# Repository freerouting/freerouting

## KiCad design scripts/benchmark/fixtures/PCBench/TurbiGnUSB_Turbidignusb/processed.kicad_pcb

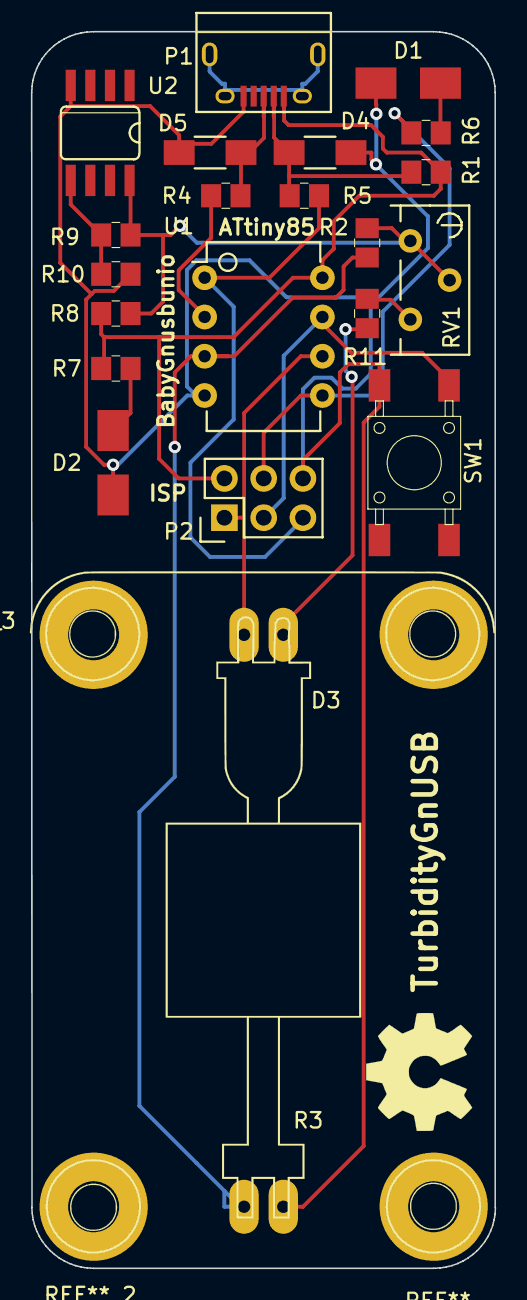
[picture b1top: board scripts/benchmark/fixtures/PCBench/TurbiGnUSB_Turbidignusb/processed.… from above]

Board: 2 copper layers, 30.0 x 80.0 mm, 22 parts (0 on the bottom side), 16 nets.

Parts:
D1, D2: LED; Fuse_SMD1206_HandSoldering
D3: LED; SolderWirePad_2x0_8_oval
D4, D5: 3.3V; C_1206_HandSoldering
P1: USB_OTG; USB_Micro-B
P2: CONN_02X03; Pin_Header_Straight_2x03
R1: 1.5k; 0805G
R2: 470k; 0805G
R3: LDR; SolderWirePad_2x0_8_oval
R4, R5: 68; 0805G
R6: 820; 0805G
R7, R8, R11: 1k; 0805G
R9: 47k; 0805G
R10: 100k; 0805G
RV1: 100k; Potentiometer_Bourns_3296Y_3-8Zoll_Angular_ScrewUp
SW1: SW_PUSH_SMALL_H; PUSH_BUTTON_SMD
U1: ATTINY85-P; DIP-8_W7.62mm
U2: LM385; SO08

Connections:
GND: D1.1, D2.1, D4.2, D5.2, P1.5, P2.6, R3.1, R10.1, SW1.2, U1.4, U2.4
MISO: D3.1, P2.1, U1.6
MOSI: P2.4, R6.2, U1.5
unnamed: D1.2, R6.1
unnamed: D2.2, R7.1
unnamed: D3.2, R11.1
unnamed: D4.1, P1.2, R1.2, R5.2
unnamed: D5.1, P1.3, R4.2
unnamed: R2.1, R3.2, U1.3
unnamed: R4.1, U1.2
unnamed: R9.1, R10.2, U2.5
unnamed: R11.2, RV1.3
REF: R2.2, R8.1, R9.2, RV1.1, RV1.2, U2.8
RESET: P2.5, R5.1, U1.1
SCK: P2.3, SW1.1, U1.7
VCC: P1.1, P2.2, R1.1, R7.2, R8.2, U1.8

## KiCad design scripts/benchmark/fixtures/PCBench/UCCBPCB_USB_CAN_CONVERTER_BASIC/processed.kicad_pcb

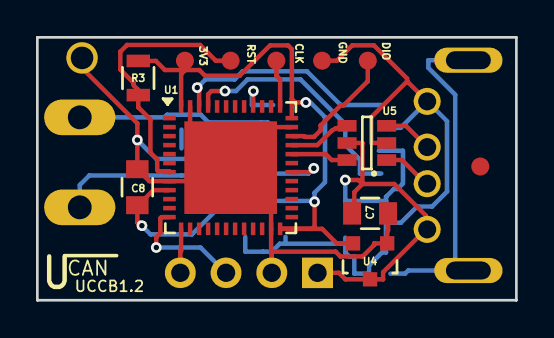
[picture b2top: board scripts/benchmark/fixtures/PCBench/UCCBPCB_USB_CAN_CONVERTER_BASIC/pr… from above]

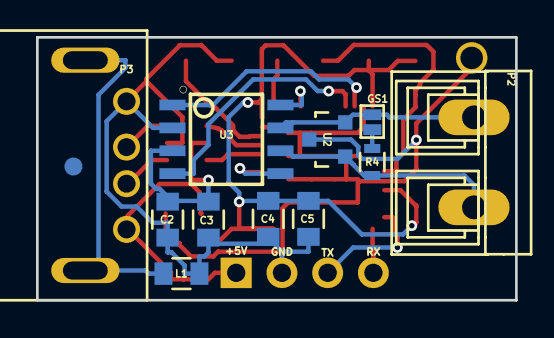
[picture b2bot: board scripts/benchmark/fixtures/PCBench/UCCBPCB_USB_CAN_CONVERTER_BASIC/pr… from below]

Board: 2 copper layers, 26.6 x 14.6 mm, 21 parts (11 on the bottom side), 20 nets.

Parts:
C2, C5: 100n; C_0805
C3, C4: 10n; C_0805
C7, C8: 1u; C_0805
F1: fiducial; Fiducial_1mm_Dia_2.54mm_Outer_CopperTop
F2: fiducial; Fiducial_1mm_Dia_2.54mm_Outer_CopperBottom
GS1: GS2; GS2s
L1: 30R@100MHz; C_0805
P1: CONN_01X05; swd_smd_conn5
P2: CONN_01X02; AK300-2MIRROR
P3: USB_A; USB_A_DS1097R
P4: CONN_01X04; Pin_Header_Angled_1x04m
R3: 10k; R_0805
R4: 120R; R_0603
U1: STM32F042C6Ux; QFN-48-1EP_7x7mm_Pitch0.5mm
U2: PESD2CAN; SOT-23
U3: TCAN332; SO
U4: MCP1700T-3302E/TT; SOT-23
U5: USBLC6-2SC6; SOT-23-6

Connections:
+3V3: C4.1, C5.1, C8.1, P1.1, R3.2, U1.9, U1.24, U1.36, U1.48, U4.2
+5V: C2.1, C3.1, C7.1, P3.1, P4.1, U3.3, U4.3, U5.5
/USART_RX: P4.4, U1.13
/USART_TX: P4.3, U1.12
CAN_MOD: U1.40, U3.8
CAN_MOD2: U1.30, U3.5
CAN_RX: U1.45, U3.4
CAN_TX: U1.46, U3.1
GND: C2.2, C3.2, C4.2, C5.2, C7.2, C8.2, L1.1, P1.4, P3.4, P4.2, U1.8, U1.23, U1.35, U1.47, U1.49, U2.3, U3.2, U4.1, U5.2
unnamed: GS1.1, R4.1
unnamed: GS1.2, P2.2, U2.2, U3.7
unnamed: L1.2, P3.5
unnamed: P1.2, R3.1, U1.7
unnamed: P2.1, R4.2, U2.1, U3.6
unnamed: P3.2, U5.1
unnamed: P3.3, U5.3
unnamed: U1.32, U5.6
unnamed: U1.33, U5.4
SW_CLK: P1.3, U1.37
SW_DIO: P1.5, U1.34

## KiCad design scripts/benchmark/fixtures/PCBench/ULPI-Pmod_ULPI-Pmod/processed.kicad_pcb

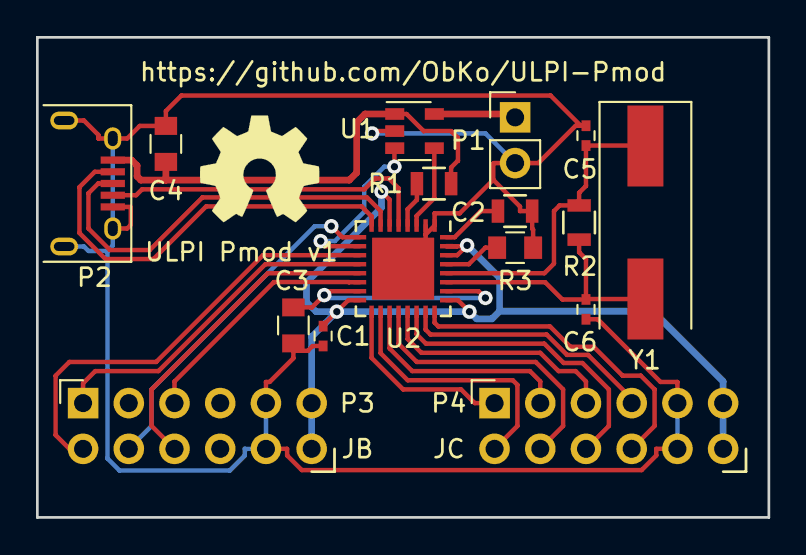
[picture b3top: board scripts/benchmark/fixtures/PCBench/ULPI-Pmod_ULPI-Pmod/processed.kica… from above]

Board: 2 copper layers, 40.6 x 26.7 mm, 16 parts (0 on the bottom side), 28 nets.

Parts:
C1: 100nF; C_0402
C2, C3, C4: 4.7μF; C_0805
C5, C6: 22pF; C_0402
P1: CONN_01X02; Pin_Header_Straight_1x02_Pitch2.54mm
P2: USB_OTG; USB_Micro-B
P3: JB; Pmod
P4: JC; Pmod
R1: 820; R_0805
R2: 1M; R_0805
R3: 12k; R_0805
U1: STMPS2141; SOT-23-5
U2: USB3300; QFN-32-1EP_5x5mm_Pitch0.5mm
Y1: Crystal; Crystal_SMD_HC49-SD

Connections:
+3V3: C1.1, P3.11, P3.12, P4.11, P4.12, U2.6, U2.16, U2.25, U2.30, U2.31
+5V: P1.1, U1.5
/CPEN: U1.4, U2.3
/D+: P2.3, U2.7
/D-: P2.2, U2.8
/EXTVBUS: U1.3, U2.10
/ULPI_CLK: P3.5, U2.14
/ULPI_DATA0: P4.8, U2.24
/ULPI_DATA1: P4.7, U2.23
/ULPI_DATA2: P4.6, U2.22
/ULPI_DATA3: P4.5, U2.21
/ULPI_DATA4: P4.4, U2.20
/ULPI_DATA5: P4.3, U2.19
/ULPI_DATA6: P4.2, U2.18
/ULPI_DATA7: P4.1, U2.17
/ULPI_DIR: P3.1, U2.12
/ULPI_NXT: P3.2, U2.11
/ULPI_RESET: P3.4, U2.9
/ULPI_STP: P3.6, U2.13
GND: C1.2, C2.2, C3.2, C4.2, C5.2, C6.2, P1.2, P2.5, P2.6, P3.9, P3.10, P4.9, P4.10, R3.2, U1.2, U2.1, U2.2, U2.33
unnamed: C2.1, U2.29
unnamed: C3.1, U2.15, U2.26
unnamed: C4.1, P2.1, R1.2, U1.1
unnamed: C5.1, R2.2, U2.28, Y1.1
unnamed: C6.1, R2.1, U2.27, Y1.2
unnamed: P2.4, U2.5
unnamed: R1.1, U2.4
unnamed: R3.1, U2.32
